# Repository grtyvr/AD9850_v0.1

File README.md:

# AD9850_v0.1
Initial version of the 328p based AD9850 function generator.

It is based on the project:

http://www.vwlowen.co.uk/arduino/AD9850-waveform-generator/AD9850-waveform-generator.htm

Which in turn is based on AD9851 code from Andrew Smallbone - modified for AD9850
   http://www.rocketnumbernine.com/2011/10/25/programming-the-ad9851-dds-synthesizer

I have created the KiCad files for a board for this project.

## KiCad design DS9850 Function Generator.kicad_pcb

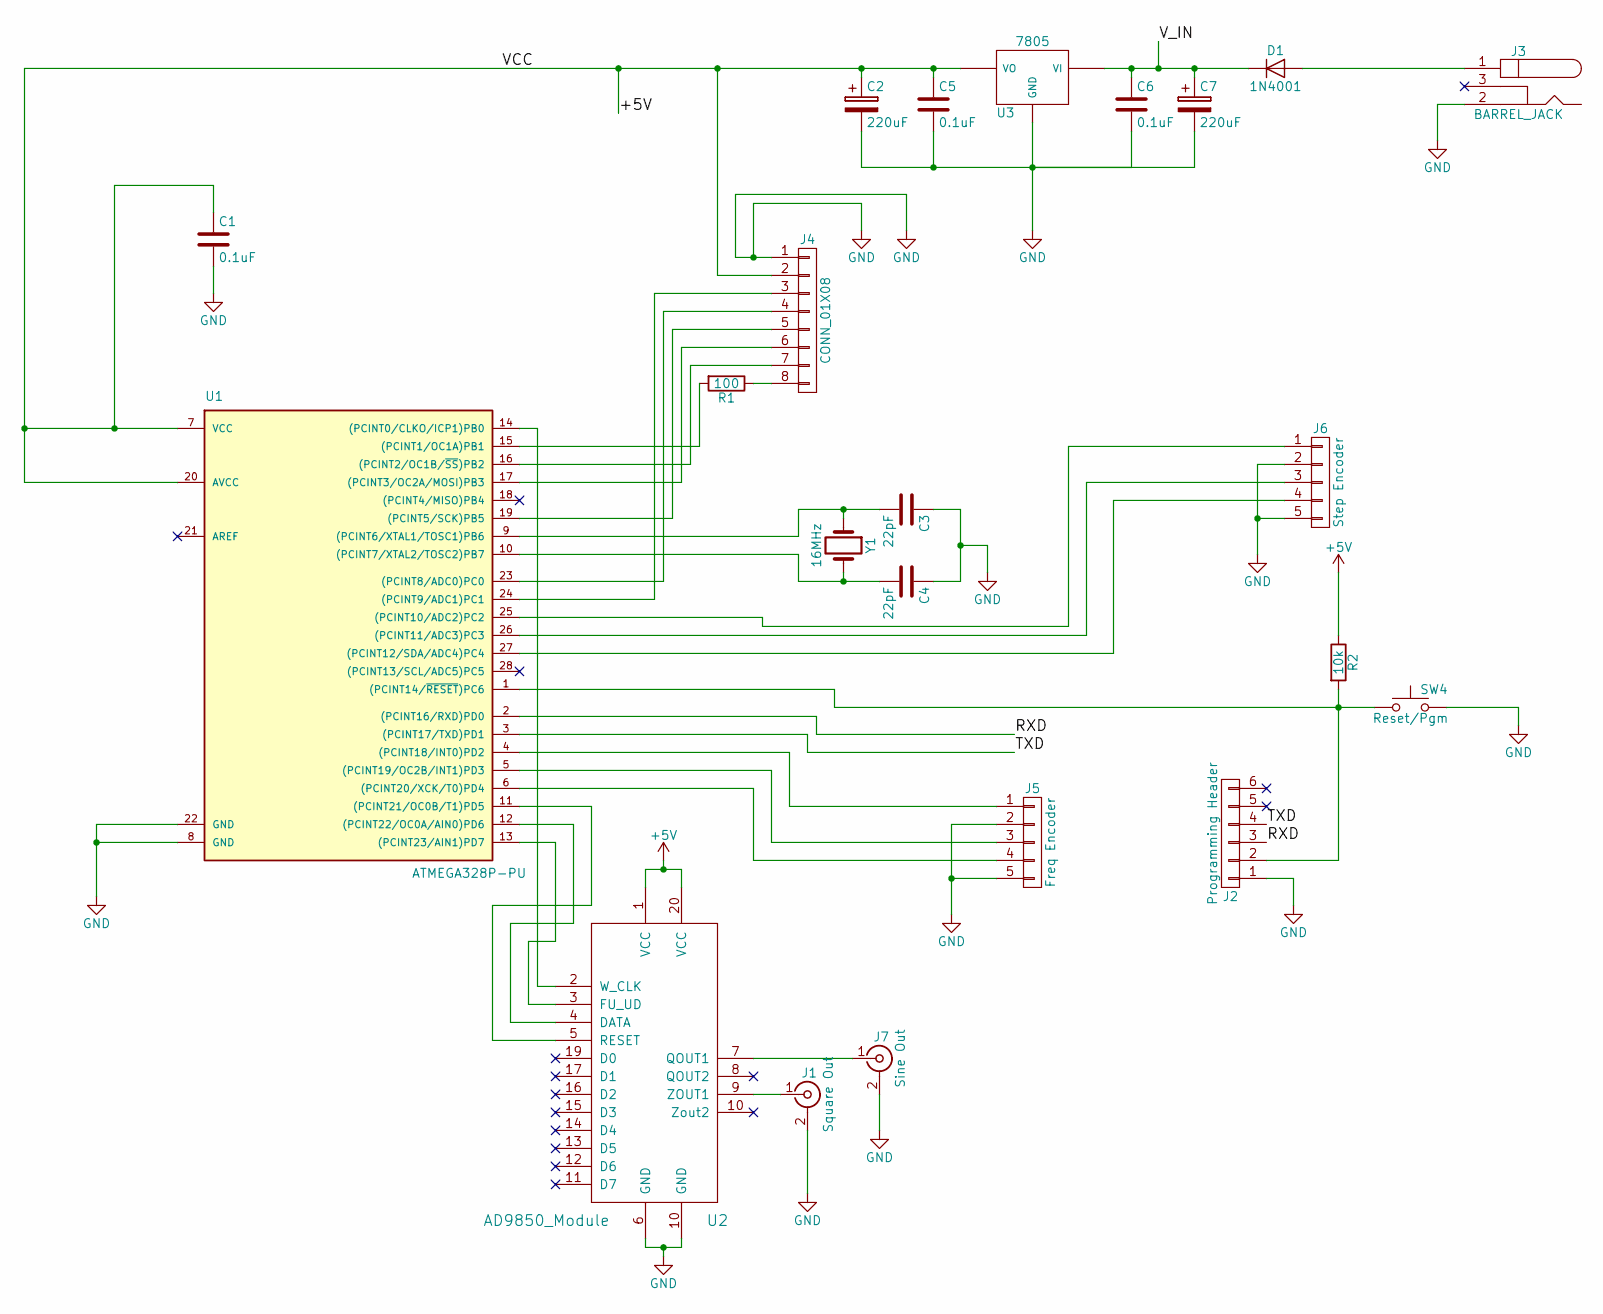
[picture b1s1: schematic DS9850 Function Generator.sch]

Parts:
C1, C5: 0.1uF; C_Disc_D3.0mm_W1.6mm_P2.50mm
C2, C7: 220uF; CP_Radial_D8.0mm_P3.50mm
C3, C4: 22pF; C_Disc_D3.0mm_W1.6mm_P2.50mm
C6: 0.1uF; C_Disc_D3.0mm_W2.0mm_P2.50mm
D1: 1N4001; D_A-405_P10.16mm_Horizontal
J1: Square Out; BNC_Socket_TYCO-AMP
J2: Programming Header; Pin_Header_Straight_1x06_Pitch2.54mm
J3: BARREL_JACK
J4: CONN_01X08; JST_EH_B08B-EH-A_08x2.50mm_Straight
J5: Freq Encoder; JST_EH_B05B-EH-A_05x2.50mm_Straight
J6: Step Encoder; JST_EH_B05B-EH-A_05x2.50mm_Straight
J7: Sine Out; BNC_Socket_TYCO-AMP
R1: 100; R3-5
R2: 10k; D3
SW4: Reset/Pgm; SW_PUSH_6mm
U1: ATMEGA328P-PU; DIP-28_W7.62mm
U2: AD9850_Module; DS9850_Module
U3: 7805
Y1: 16MHz; Crystal_AT310_d3.0mm_l10.0mm_Horizontal

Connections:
+5V: C1.1, C2.1, C5.1, J4.2, R2.1, U1.7 (VCC), U1.20 (AVCC), U2.1 (VCC), U2.20 (VCC), U3.VO
/RXD: J2.3, U1.2 ((PCINT16/RXD)PD0)
/TXD: J2.4, U1.3 ((PCINT17/TXD)PD1)
/V_IN: C6.1, C7.1, D1.1 (K), U3.VI
unnamed: C3.2, U1.9 ((PCINT6/XTAL1/TOSC1)PB6), Y1.1
unnamed: C4.2, U1.10 ((PCINT7/XTAL2/TOSC2)PB7), Y1.2
unnamed: D1.2 (A), J3.1
unnamed: J1.1 (In), U2.9 (ZOUT1)
unnamed: J2.2, R2.2, SW4.1, U1.1 ((PCINT14/~RESET~)PC6)
unnamed: J4.3, U1.24 ((PCINT9/ADC1)PC1)
unnamed: J4.4, U1.23 ((PCINT8/ADC0)PC0)
unnamed: J4.5, U1.19 ((PCINT5/SCK)PB5)
unnamed: J4.6, U1.17 ((PCINT3/OC2A/MOSI)PB3)
unnamed: J4.7, U1.16 ((PCINT2/OC1B/~SS~)PB2)
unnamed: J4.8, R1.1
unnamed: J5.1, U1.4 ((PCINT18/INT0)PD2)
unnamed: J5.3, U1.5 ((PCINT19/OC2B/INT1)PD3)
unnamed: J5.4, U1.6 ((PCINT20/XCK/T0)PD4)
unnamed: J6.1, U1.25 ((PCINT10/ADC2)PC2)
unnamed: J6.3, U1.26 ((PCINT11/ADC3)PC3)
unnamed: J6.4, U1.27 ((PCINT12/SDA/ADC4)PC4)
unnamed: J7.1 (In), U2.7 (QOUT1)
unnamed: R1.2, U1.15 ((PCINT1/OC1A)PB1)
unnamed: U1.11 ((PCINT21/OC0B/T1)PD5), U2.5 (RESET)
unnamed: U1.12 ((PCINT22/OC0A/AIN0)PD6), U2.4 (DATA)
unnamed: U1.13 ((PCINT23/AIN1)PD7), U2.3 (FU_UD)
unnamed: U1.14 ((PCINT0/CLKO/ICP1)PB0), U2.2 (W_CLK)

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
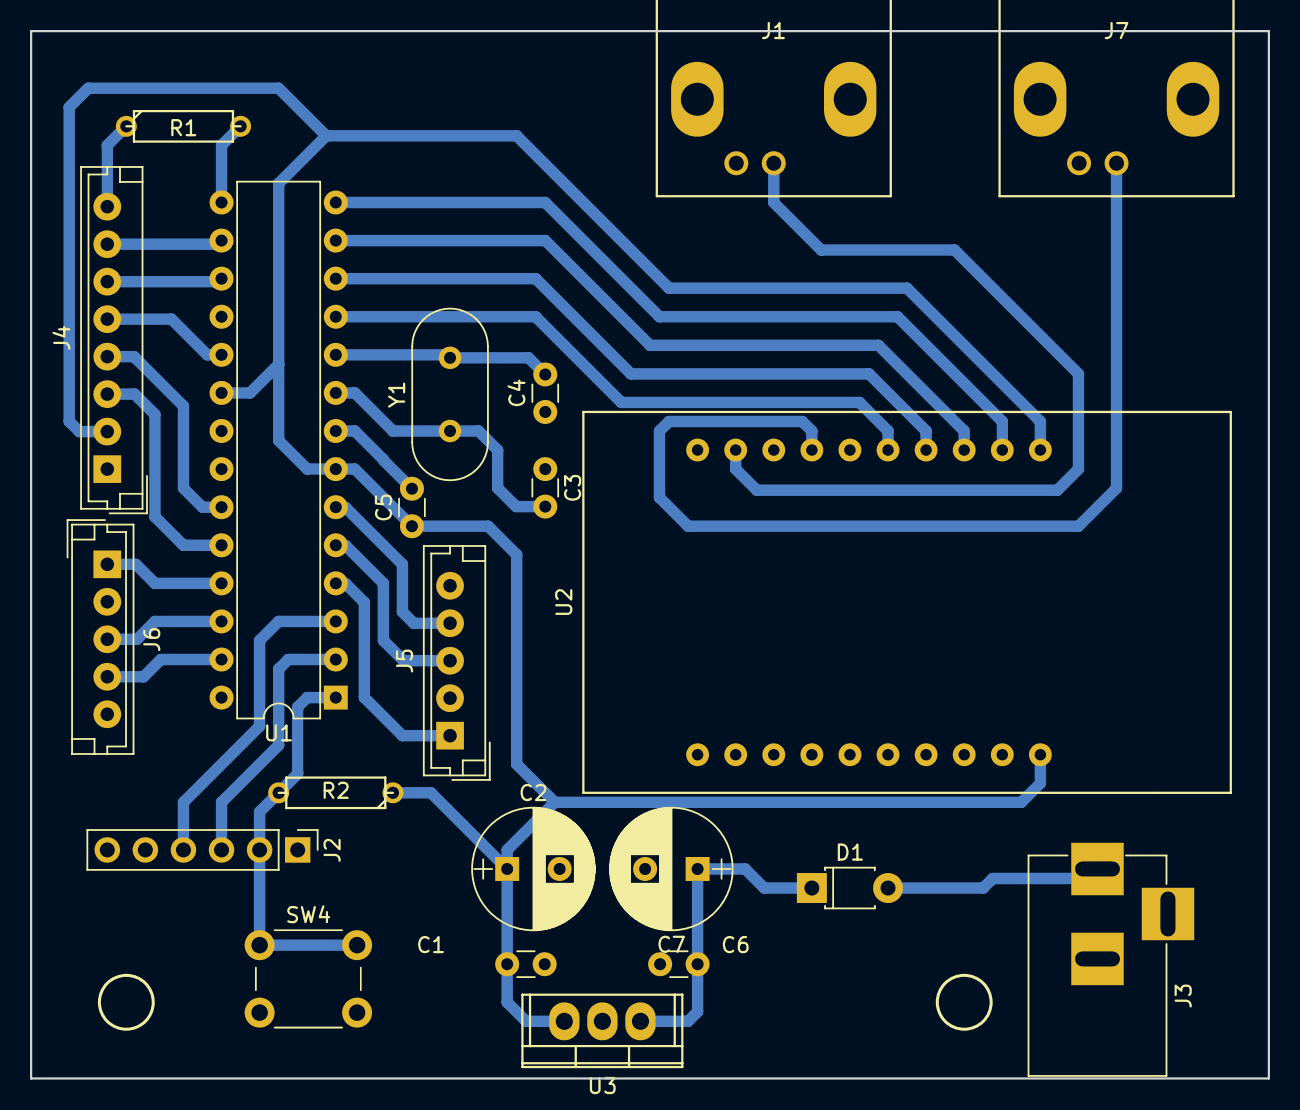
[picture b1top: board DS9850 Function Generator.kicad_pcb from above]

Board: 2 copper layers, 82.6 x 69.9 mm, 22 parts (0 on the bottom side), 28 nets.

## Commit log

2018-02-23 Update README.md
    Added the history of the project and describe what I have added to it. (not much :0
2018-02-23 Update LICENSE
    removed MIT put in CC
